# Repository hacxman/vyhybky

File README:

High pass a low pass vyhybky 8. radu, Sallen-Key architektura, Butterworthov filter.
Schema vyhybiek LP + HP - vyhybka.sch.
PCB su rozdelene do lowpass.kicad_pcb a highpass_kicad_pcb kvoli freeroutingu

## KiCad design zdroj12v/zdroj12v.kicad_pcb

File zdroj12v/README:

vyrobili sme routovatelny_12v.kicad_pcb

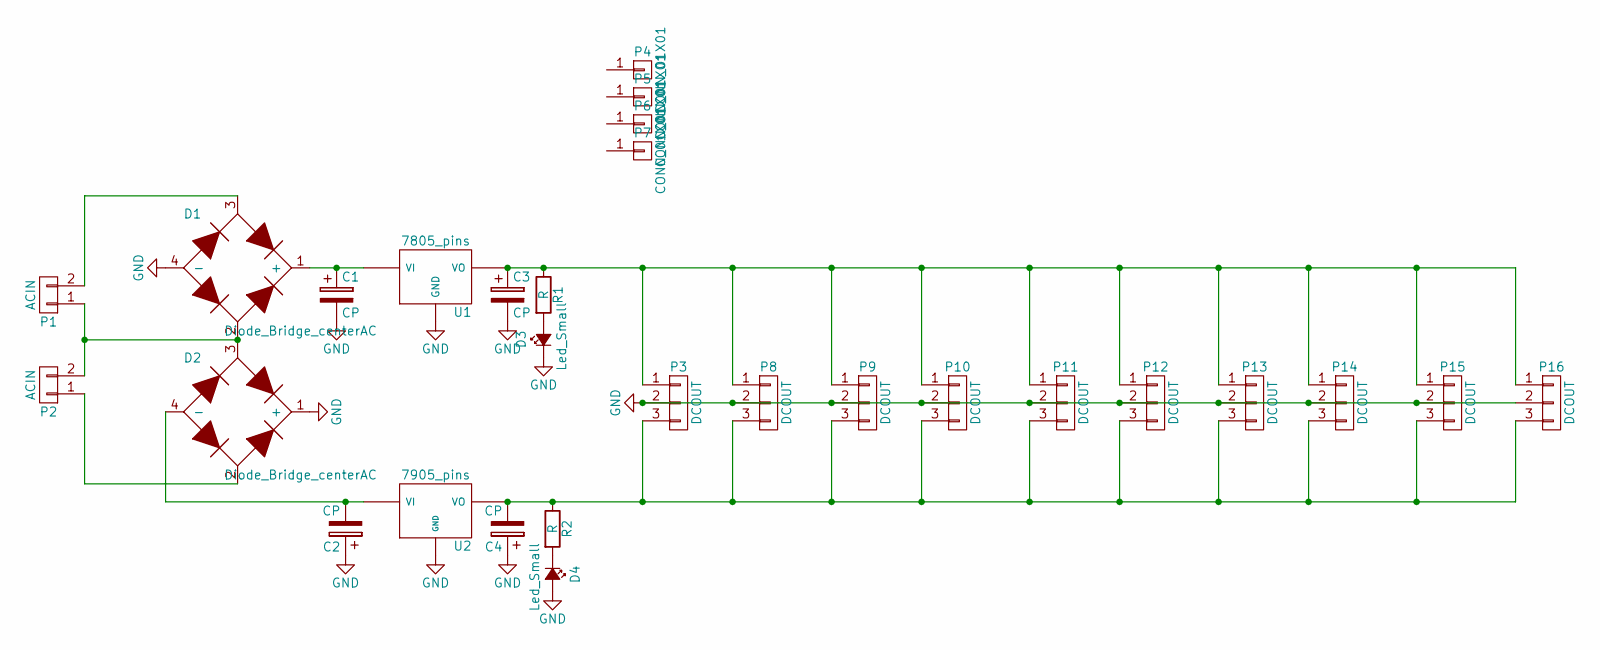
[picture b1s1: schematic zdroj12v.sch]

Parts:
C1, C2: CP; C_Radial_D18_L36_P7.5
C3, C4: CP; c_elec_6.3x7.7
D1, D2: Diode_Bridge_centerAC; GSIB
D3, D4: Led_Small; LED-1206
P1, P2: ACIN; TerminalBlock_Pheonix_MKDS1.5-2pol
P3, P8, P9, P10, P11, P12, P13, P14, P15, P16: DCOUT; TerminalBlock_Pheonix_MKDS1.5-3pol
P4, P5, P6, P7: CONN_01X01; MountingHole_3mm
R1, R2: R; R_0603_HandSoldering
U1: 7805_pins; TO-220_Neutral123_Vertical_LargePads
U2: 7905_pins; TO-220_Neutral123_Vertical_LargePads

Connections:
GND: C1.2, C2.1, C3.2, C4.1, D1.4 (-), D2.1 (+), D3.1 (K), D4.2 (A), P3.2, P8.2, P9.2, P10.2, P11.2, P12.2, P13.2, P14.2, P15.2, P16.2, U1.2 (GND), U2.1 (GND)
unnamed: C1.1, D1.1 (+), U1.1 (VI)
unnamed: C2.2, D2.4 (-), U2.2 (VI)
unnamed: C3.1, P3.1, P8.1, P9.1, P10.1, P11.1, P12.1, P13.1, P14.1, P15.1, P16.1, R1.1, U1.3 (VO)
unnamed: C4.2, P3.3, P8.3, P9.3, P10.3, P11.3, P12.3, P13.3, P14.3, P15.3, P16.3, R2.1, U2.3 (VO)
unnamed: D1.2, D2.3, P1.1, P2.2
unnamed: D1.3, P1.2
unnamed: D2.2, P2.1
unnamed: D3.2 (A), R1.2
unnamed: D4.1 (K), R2.2

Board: 2 copper layers, 28 parts (4 on the bottom side), 10 nets, no tracks yet.

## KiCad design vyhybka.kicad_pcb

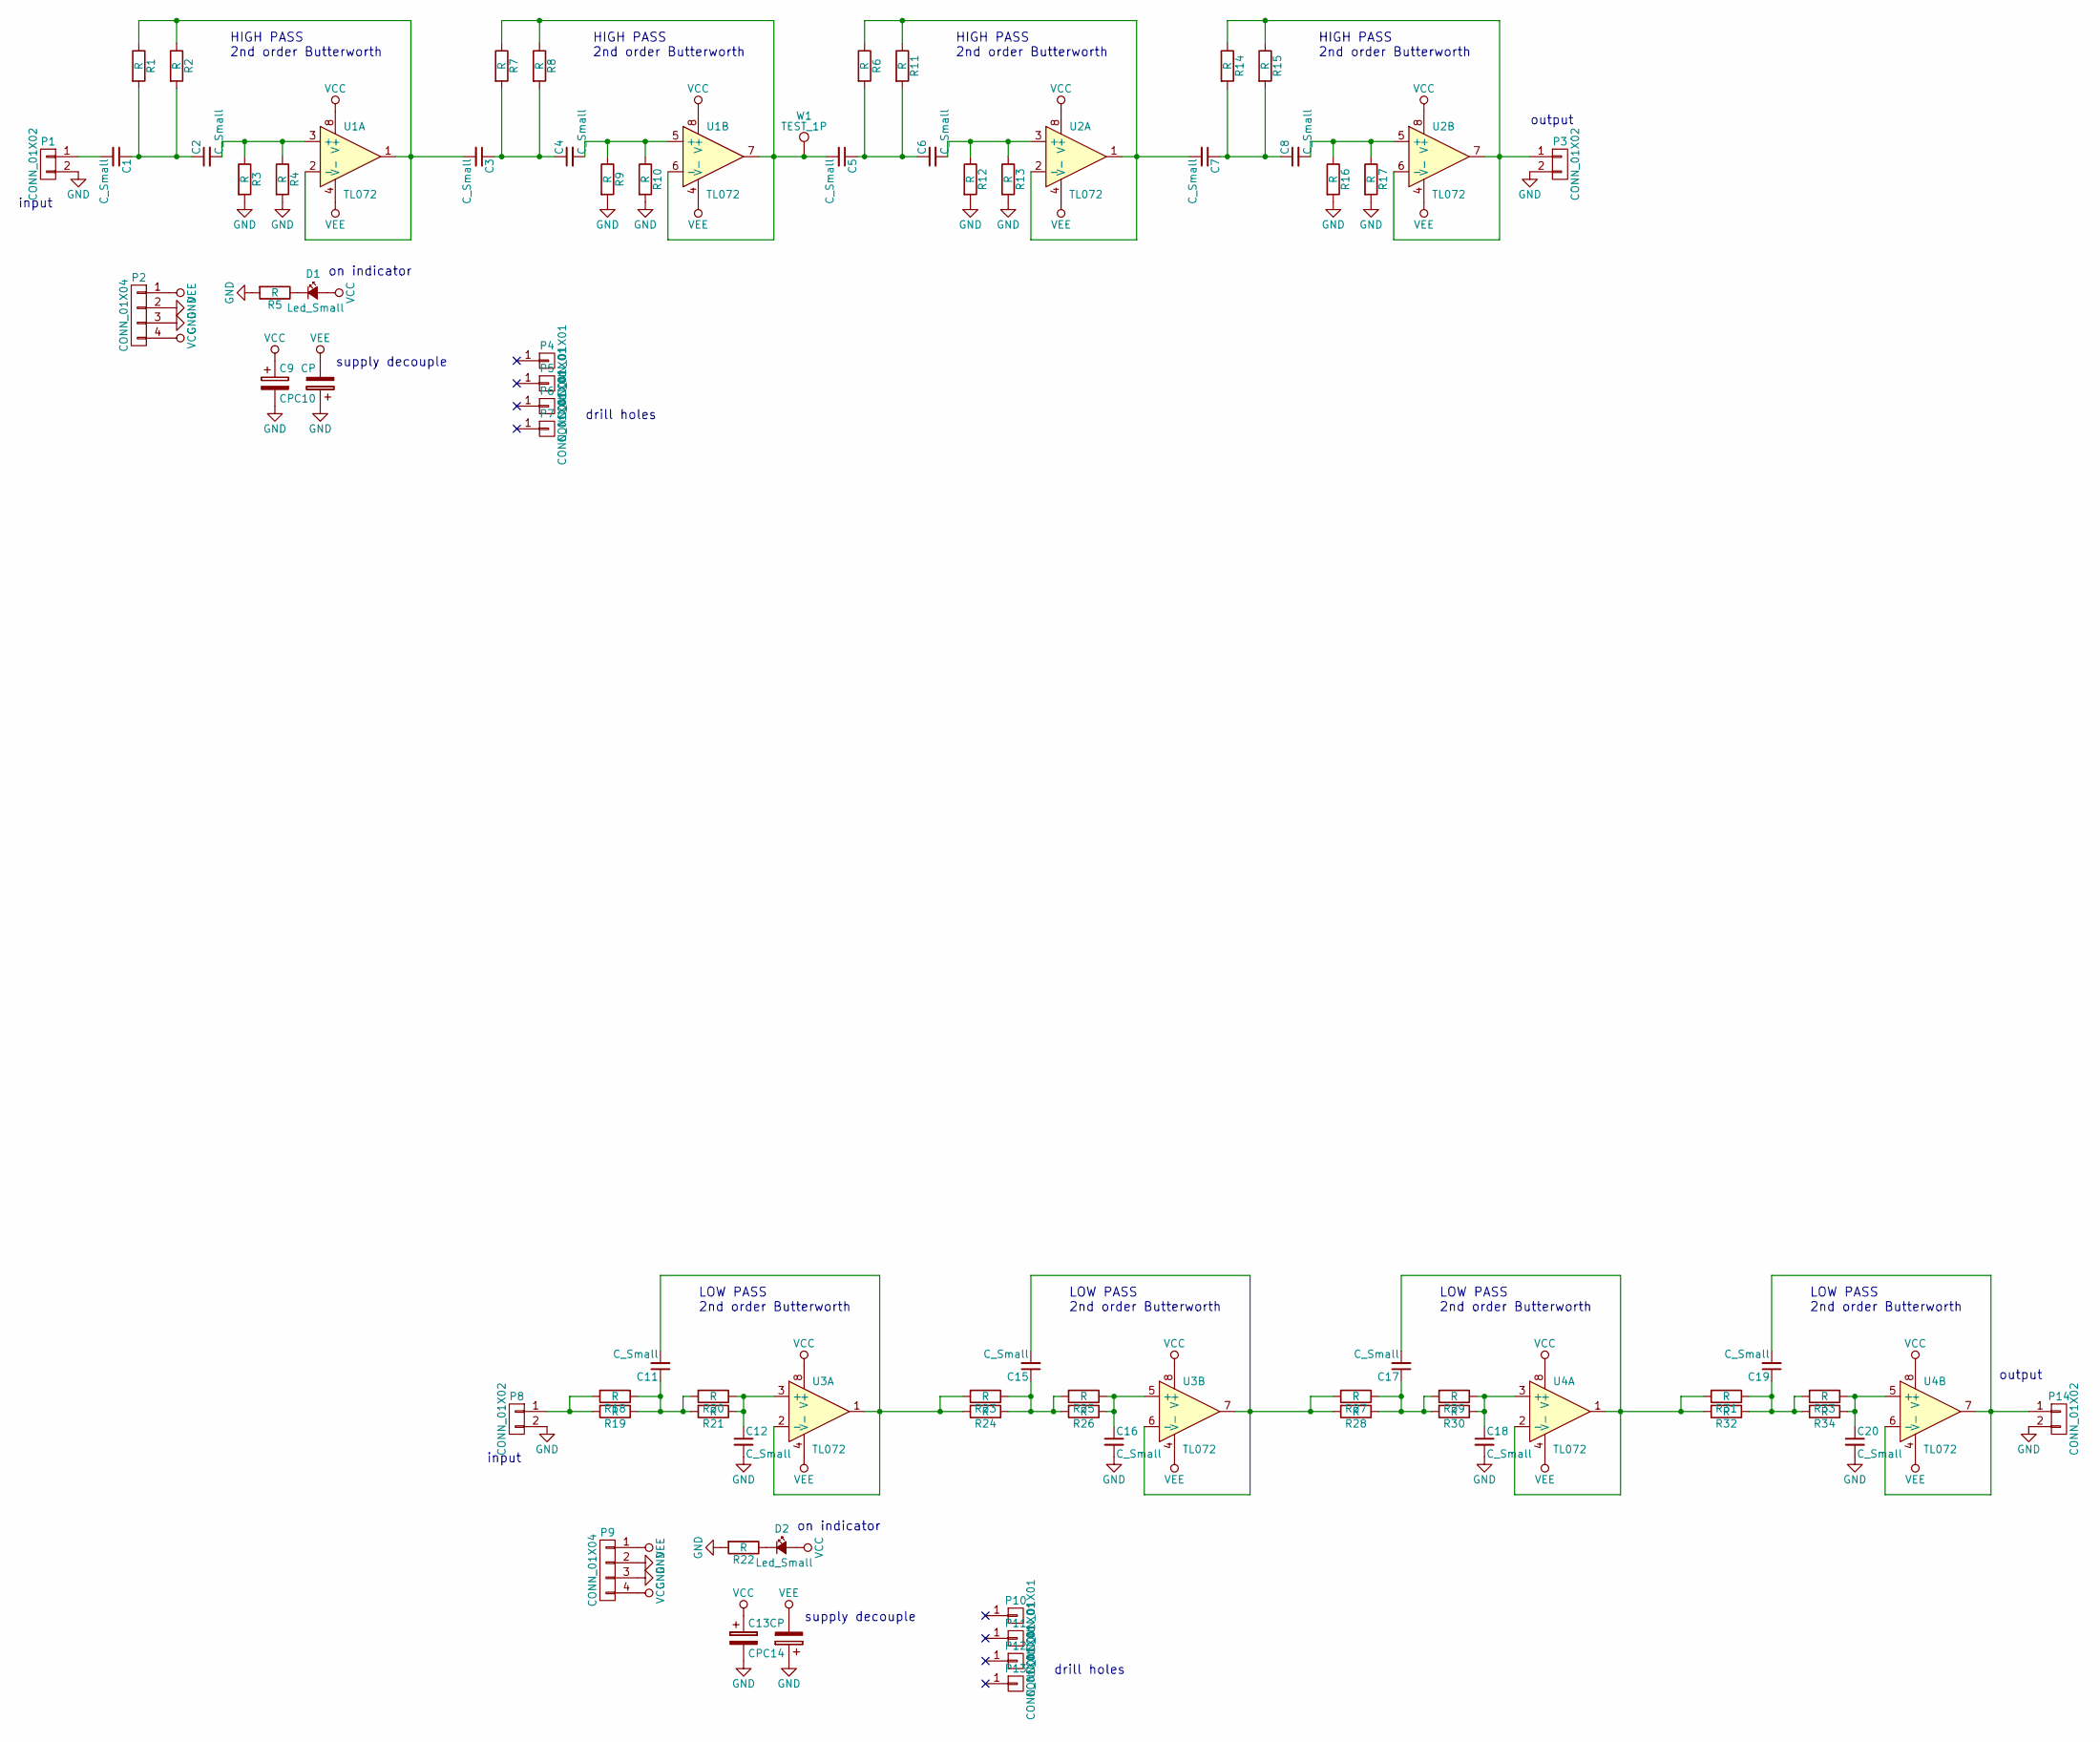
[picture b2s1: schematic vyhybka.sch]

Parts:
C1, C2, C3, C4, C5, C6, C7, C8, C11, C12, C15, C16, C17, C18, C19, C20: C_Small; C_Disc_D6_P5
C9, C10, C13, C14: CP; c_elec_5x4.5
D1, D2: Led_Small; LED-1206
P1, P3, P8, P14: CONN_01X02; TerminalBlock_Pheonix_MKDS1.5-2pol
P2, P9: CONN_01X04; TerminalBlock_Pheonix_MKDS1.5-4pol
P4, P5, P6, P7, P10, P11, P12, P13: CONN_01X01; MountingHole_3mm
R1, R2, R3, R4, R6, R7, R8, R9, R10, R11, R12, R13, R14, R15, R16, R17, R18, R19, R20, R21, R23, R24, R25, R26, R27, R28, R29, R30, R31, R32, R33, R34: R; Resistor_Horizontal_RM10mm
R5, R22: R; R_0603_HandSoldering
U1, U2, U3, U4: TL072; DIP-8_W7.62mm_LongPads
W1: TEST_1P; Pin_Header_Straight_1x01

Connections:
GND: C9.2, C10.1, C12.2, C13.2, C14.1, C16.2, C18.2, C20.2, P1.2, P2.2, P2.3, P3.2, P8.2, P9.2, P9.3, P14.2, R3.2, R4.2, R5.2, R9.2, R10.2, R12.2, R13.2, R16.2, R17.2, R22.2
unnamed: C1.1, C2.1, R1.2, R2.2
unnamed: C1.2, P1.1
unnamed: C2.2, R3.1, R4.1, U1.3 (+)
unnamed: C3.1, C4.1, R7.2, R8.2
unnamed: C3.2, R1.1, R2.1, U1.1, U1.2 (-)
unnamed: C4.2, R9.1, R10.1, U1.5 (+)
unnamed: C5.1, C6.1, R6.2, R11.2
unnamed: C5.2, R7.1, R8.1, U1.6 (-), U1.7, W1.1
unnamed: C6.2, R12.1, R13.1, U2.3 (+)
unnamed: C7.1, C8.1, R14.2, R15.2
unnamed: C7.2, R6.1, R11.1, U2.1, U2.2 (-)
unnamed: C8.2, R16.1, R17.1, U2.5 (+)
unnamed: C11.1, R18.1, R19.1, R20.2, R21.2
unnamed: C11.2, R23.2, R24.2, U3.1, U3.2 (-)
unnamed: C12.1, R20.1, R21.1, U3.3 (+)
unnamed: C15.1, R23.1, R24.1, R25.2, R26.2
unnamed: C15.2, R27.2, R28.2, U3.6 (-), U3.7
unnamed: C16.1, R25.1, R26.1, U3.5 (+)
unnamed: C17.1, R27.1, R28.1, R29.2, R30.2
unnamed: C17.2, R31.2, R32.2, U4.1, U4.2 (-)
unnamed: C18.1, R29.1, R30.1, U4.3 (+)
unnamed: C19.1, R31.1, R32.1, R33.2, R34.2
unnamed: C19.2, P14.1, U4.6 (-), U4.7
unnamed: C20.1, R33.1, R34.1, U4.5 (+)
unnamed: D1.1 (K), R5.1
unnamed: D2.1 (K), R22.1
unnamed: P3.1, R14.1, R15.1, U2.6 (-), U2.7
unnamed: P8.1, R18.2, R19.2
VCC: C9.1, C13.1, D1.2 (A), D2.2 (A), P2.4, P9.4, U1.8 (V+), U2.8 (V+), U3.8 (V+), U4.8 (V+)
VEE: C10.2, C14.2, P2.1, P9.1, U1.4 (V-), U2.4 (V-), U3.4 (V-), U4.4 (V-)

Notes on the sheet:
HIGH PASS 2nd order Butterworth
drill holes
supply decouple
on indicator
input
output
LOW PASS 2nd order Butterworth

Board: 2 copper layers, 75 parts (8 on the bottom side), 31 nets, no tracks yet.

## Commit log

2016-08-30 very first
2016-08-30 12V PSU + README
2016-08-30 README
